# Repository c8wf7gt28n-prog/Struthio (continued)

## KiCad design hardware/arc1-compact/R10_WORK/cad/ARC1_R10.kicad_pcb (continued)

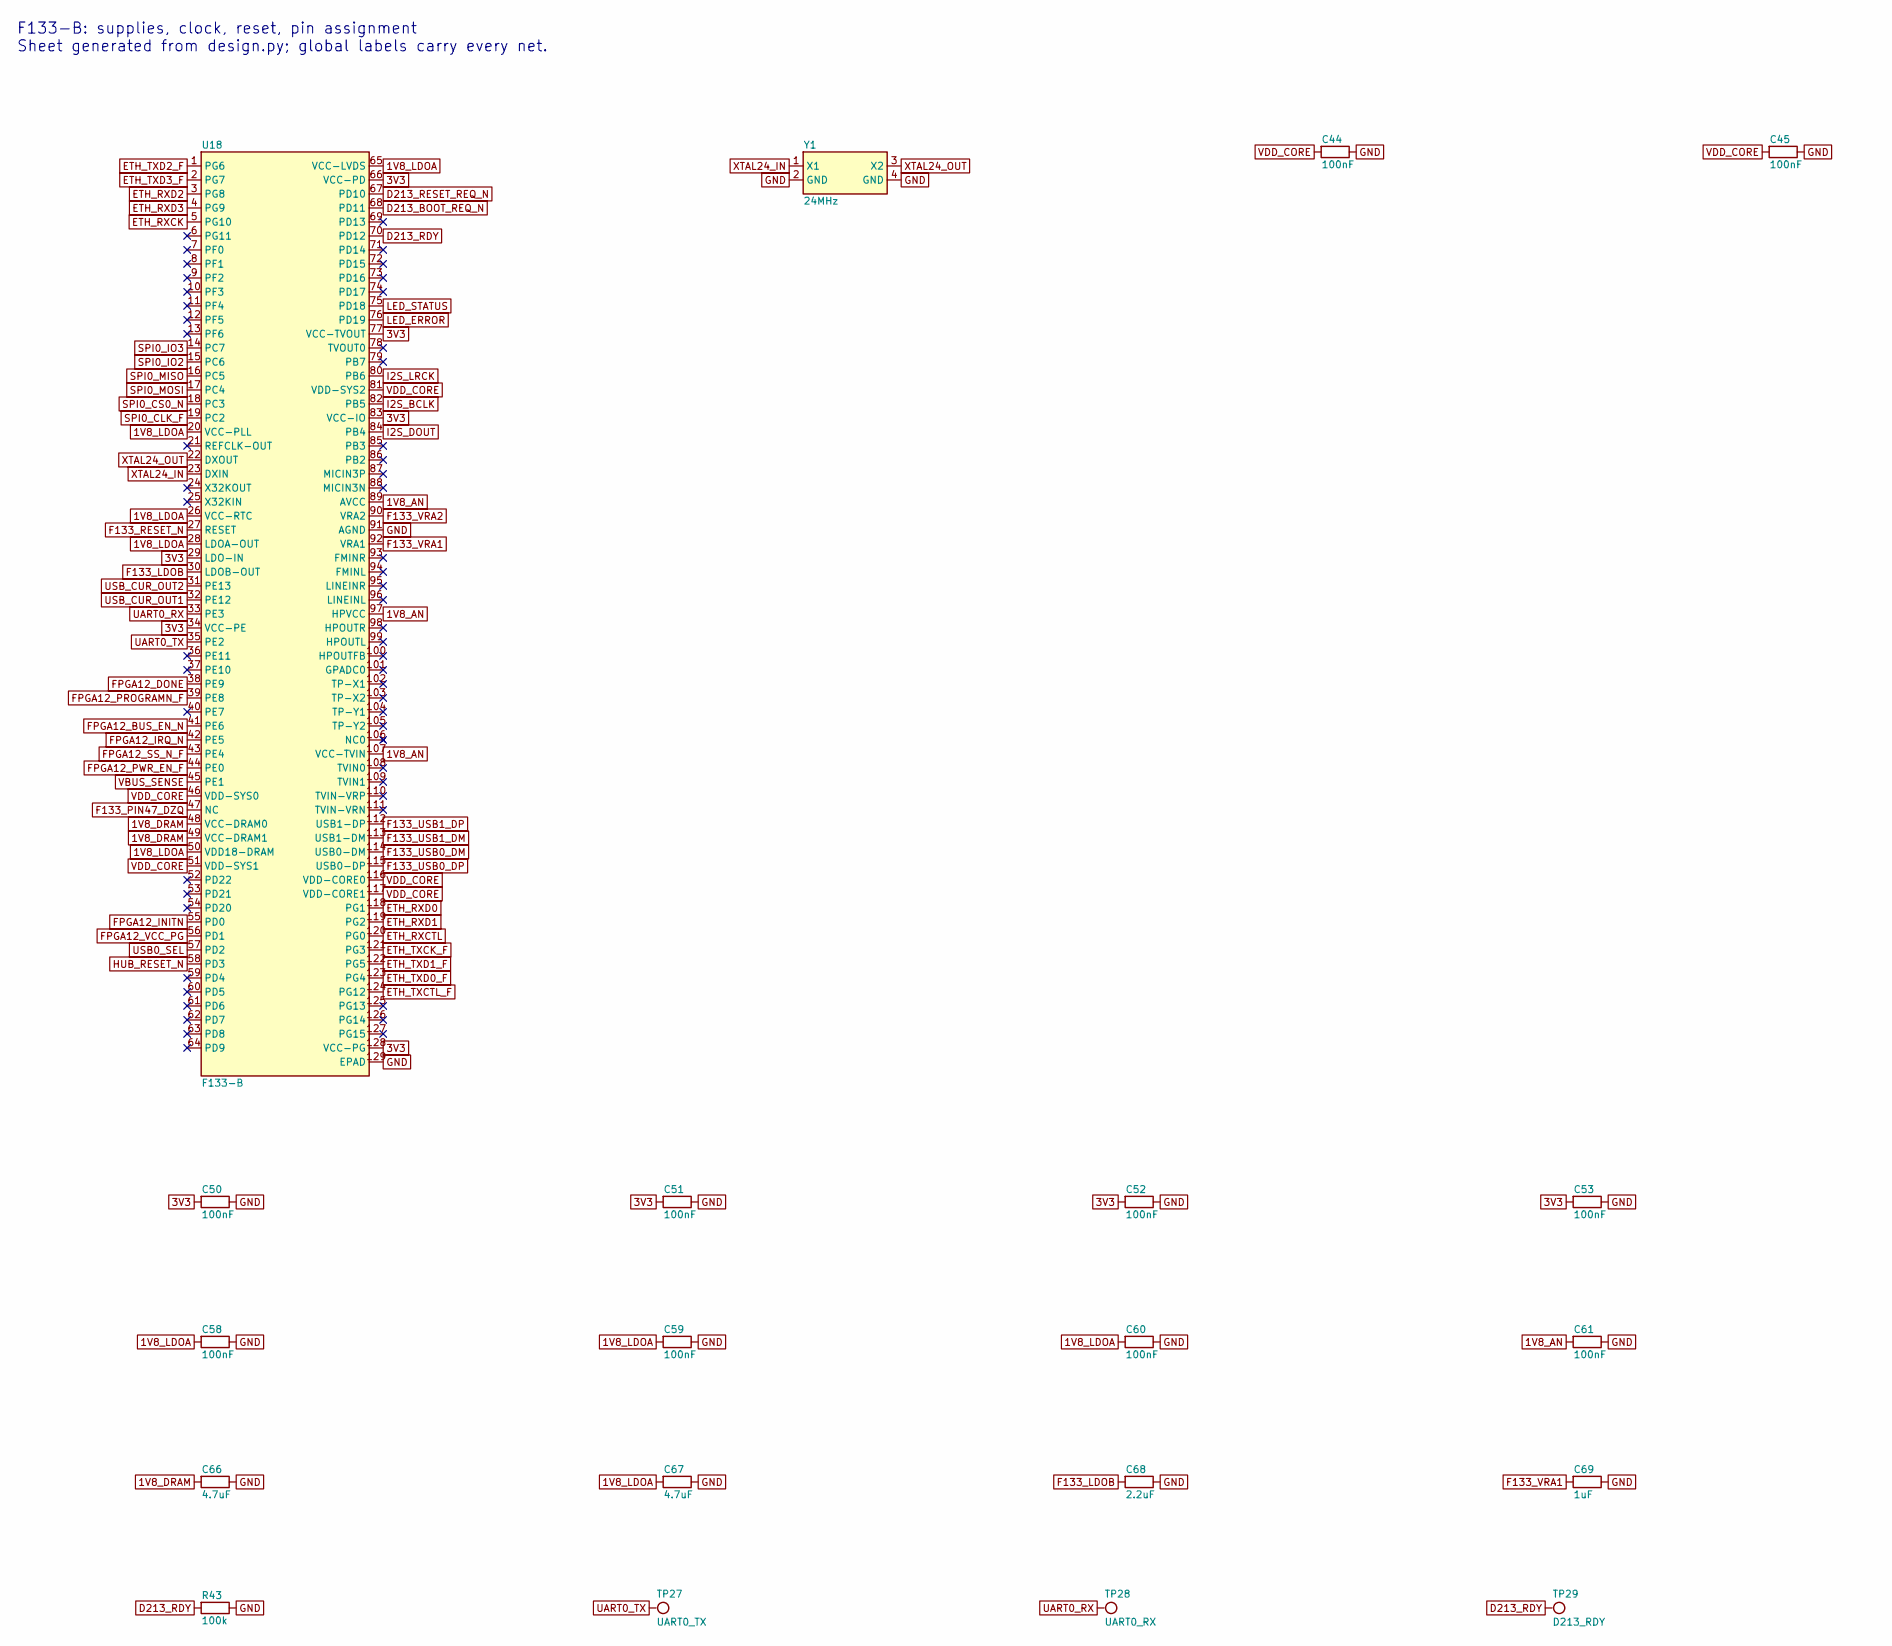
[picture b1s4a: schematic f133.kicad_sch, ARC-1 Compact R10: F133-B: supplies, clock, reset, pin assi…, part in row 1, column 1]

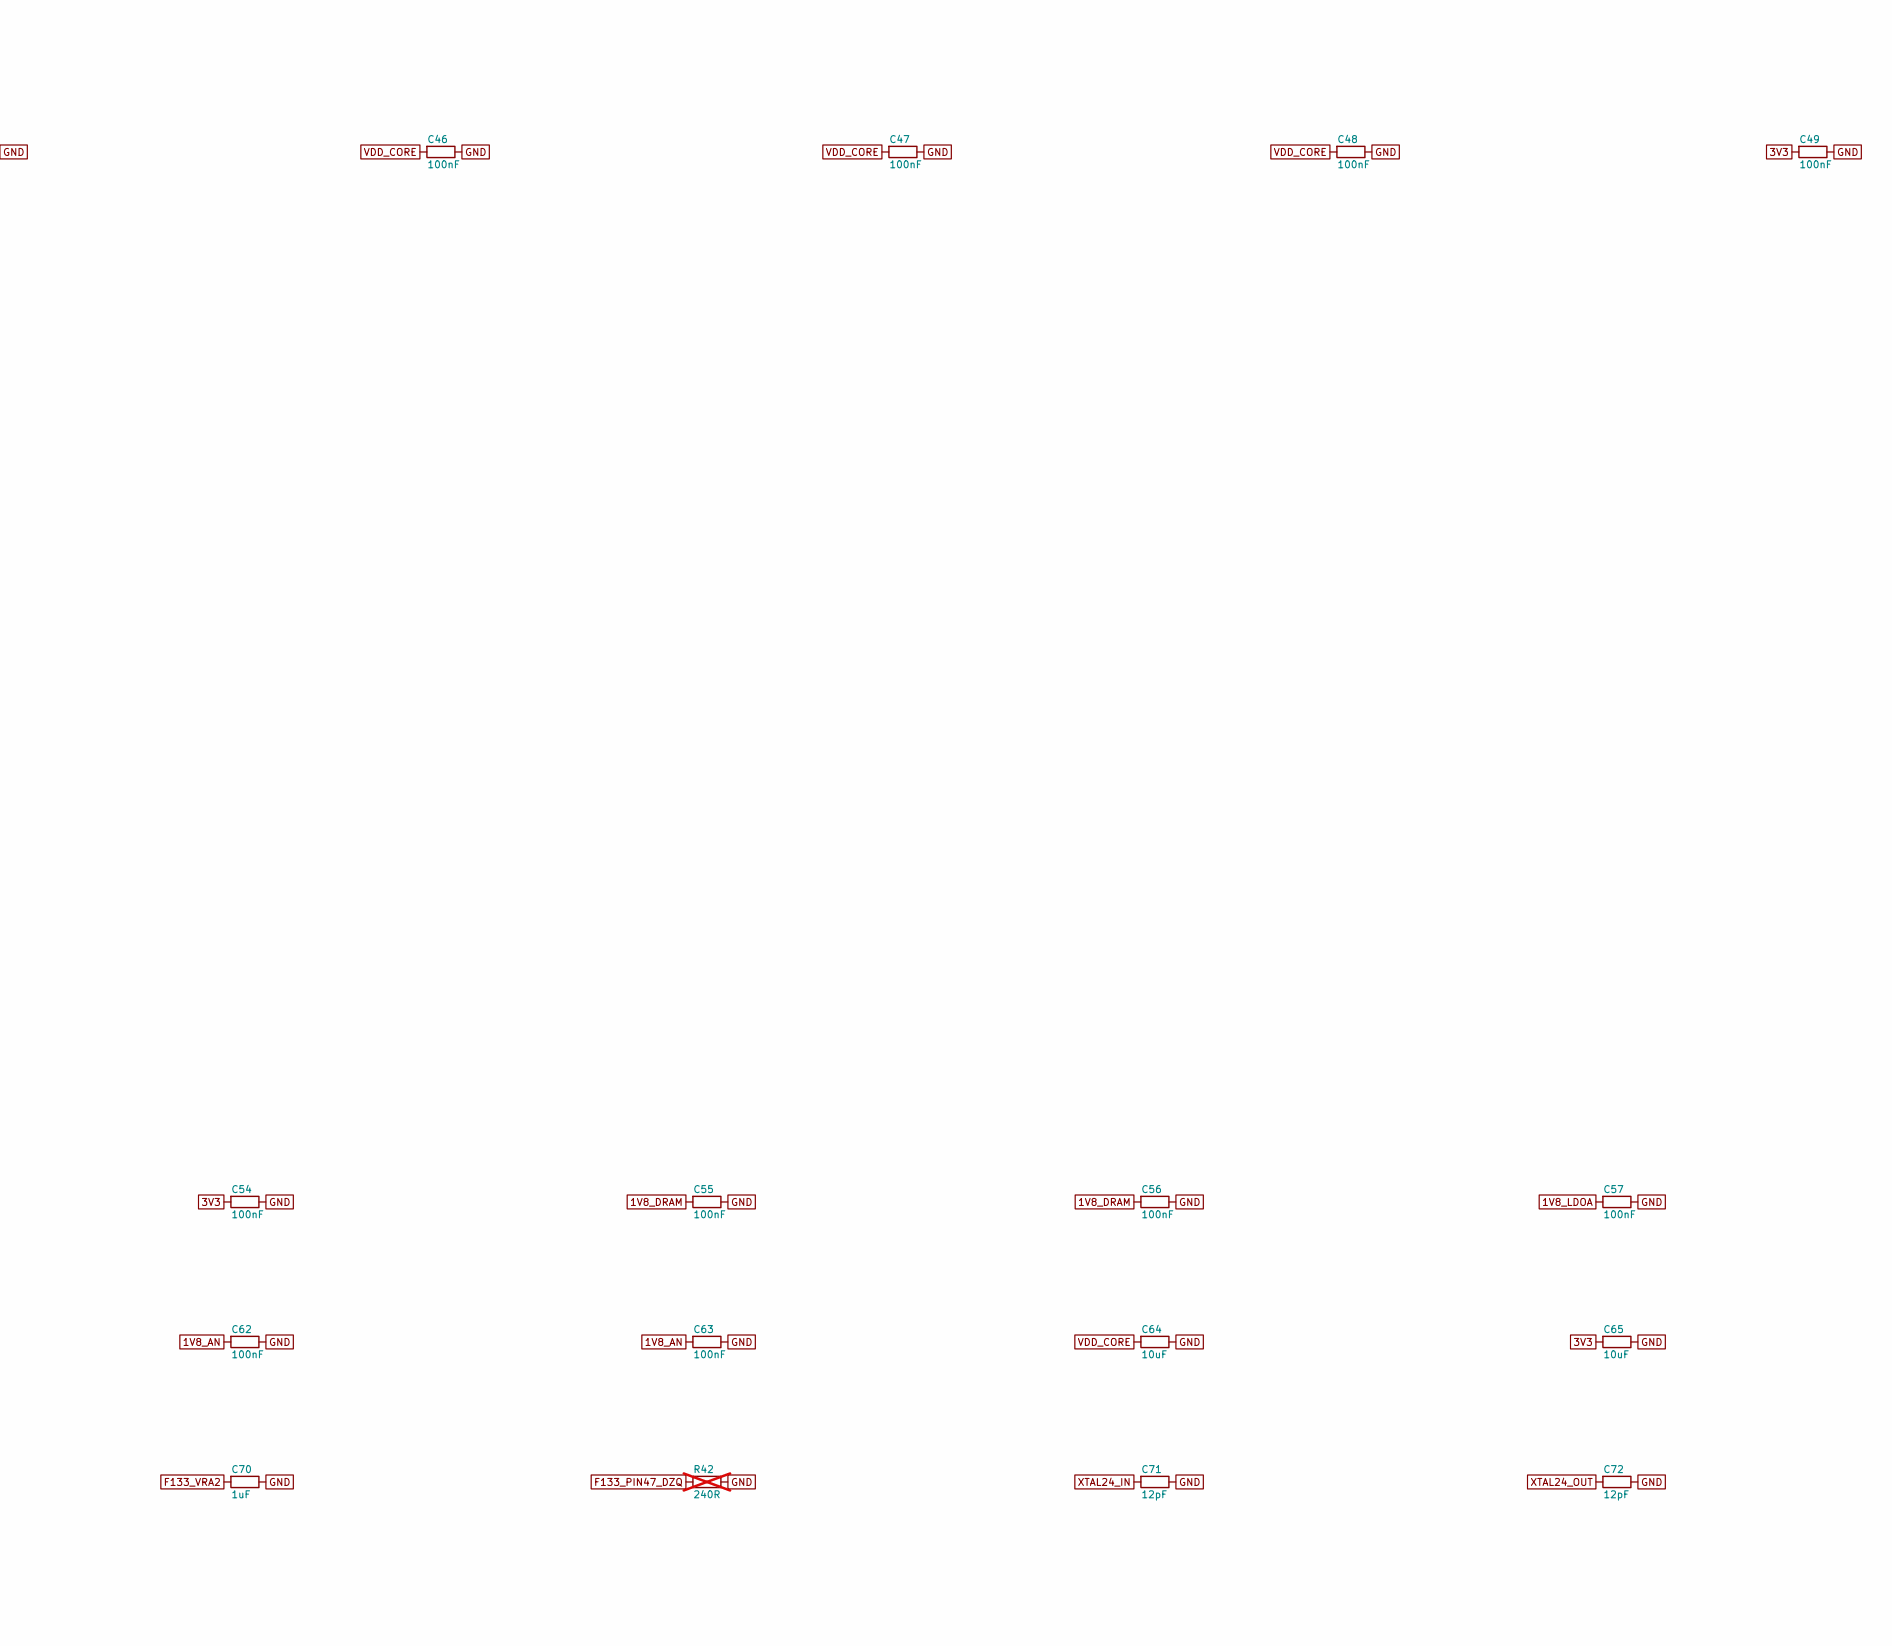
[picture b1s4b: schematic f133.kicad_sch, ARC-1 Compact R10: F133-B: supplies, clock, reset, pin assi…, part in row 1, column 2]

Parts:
C44, C45, C46, C47, C48, C49, C50, C51, C52, C53, C54, C55, C56, C57, C58, C59, C60, C61, C62, C63: 100nF; C_0402_1005Metric; MPN CL05B104KO5NNNC; LCSC C1525
C64, C65: 10uF; C_0603_1608Metric; MPN CL10A106KP8NNNC; LCSC C19702
C66, C67: 4.7uF; C_0603_1608Metric; MPN CL10A475KO8NNNC; LCSC C19666
C68: 2.2uF; C_0603_1608Metric
C69, C70: 1uF; C_0402_1005Metric; MPN CL05A105KA5NQNC; LCSC C52923
C71, C72: 12pF; C_0402_1005Metric; MPN 0402CG120J500NT; LCSC C1547
R42: 240R; R_0402_1005Metric; not fitted
R43: 100k; R_0402_1005Metric; MPN 0402WGF1003TCE; LCSC C25741
TP27: UART0_TX; TestPoint_Pad_D1.0mm
TP28: UART0_RX; TestPoint_Pad_D1.0mm
TP29: D213_RDY; TestPoint_Pad_D1.0mm
U18: F133-B; Allwinner_F133_eLQFP128_14x14_P0.4_EP5.72; MPN F133-B
Y1: 24MHz; Crystal_SMD_3225-4Pin_3.2x2.5mm; MPN 24 MHz 3225 crystal CL=12 pF +-20 ppm (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

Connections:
1V8_AN: C61.1, C62.1, C63.1, U18.89 (AVCC), U18.97 (HPVCC), U18.107 (VCC-TVIN); also elsewhere on the board
1V8_DRAM: C55.1, C56.1, C66.1, U18.48 (VCC-DRAM0), U18.49 (VCC-DRAM1); also elsewhere on the board
1V8_LDOA: C57.1, C58.1, C59.1, C60.1, C67.1, U18.20 (VCC-PLL), U18.26 (VCC-RTC), U18.28 (LDOA-OUT), U18.50 (VDD18-DRAM), U18.65 (VCC-LVDS); also elsewhere on the board
3V3: C49.1, C50.1, C51.1, C52.1, C53.1, C54.1, C65.1, U18.29 (LDO-IN), U18.34 (VCC-PE), U18.66 (VCC-PD), U18.77 (VCC-TVOUT), U18.83 (VCC-IO), U18.128 (VCC-PG); also elsewhere on the board
D213_BOOT_REQ_N: U18.68 (PD11); also elsewhere on the board
D213_RDY: R43.1, TP29.1, U18.70 (PD12); also elsewhere on the board
D213_RESET_REQ_N: U18.67 (PD10); also elsewhere on the board
ETH_RXCK: U18.5 (PG10); also elsewhere on the board
ETH_RXCTL: U18.120 (PG0); also elsewhere on the board
ETH_RXD0: U18.118 (PG1); also elsewhere on the board
ETH_RXD1: U18.119 (PG2); also elsewhere on the board
ETH_RXD2: U18.3 (PG8); also elsewhere on the board
ETH_RXD3: U18.4 (PG9); also elsewhere on the board
ETH_TXCK_F: U18.121 (PG3); also elsewhere on the board
ETH_TXCTL_F: U18.124 (PG12); also elsewhere on the board
ETH_TXD0_F: U18.123 (PG4); also elsewhere on the board
ETH_TXD1_F: U18.122 (PG5); also elsewhere on the board
ETH_TXD2_F: U18.1 (PG6); also elsewhere on the board
ETH_TXD3_F: U18.2 (PG7); also elsewhere on the board
F133_LDOB: C68.1, U18.30 (LDOB-OUT)
F133_PIN47_DZQ: R42.1, U18.47 (NC)
F133_RESET_N: U18.27 (RESET); also elsewhere on the board
F133_USB0_DM: U18.114 (USB0-DM); also elsewhere on the board
F133_USB0_DP: U18.115 (USB0-DP); also elsewhere on the board
F133_USB1_DM: U18.113 (USB1-DM); also elsewhere on the board
F133_USB1_DP: U18.112 (USB1-DP); also elsewhere on the board
F133_VRA1: C69.1, U18.92 (VRA1)
F133_VRA2: C70.1, U18.90 (VRA2)
FPGA12_BUS_EN_N: U18.41 (PE6); also elsewhere on the board
FPGA12_DONE: U18.38 (PE9); also elsewhere on the board
FPGA12_INITN: U18.55 (PD0); also elsewhere on the board
FPGA12_IRQ_N: U18.42 (PE5); also elsewhere on the board
FPGA12_PROGRAMN_F: U18.39 (PE8); also elsewhere on the board
FPGA12_PWR_EN_F: U18.44 (PE0); also elsewhere on the board
FPGA12_SS_N_F: U18.43 (PE4); also elsewhere on the board
FPGA12_VCC_PG: U18.56 (PD1); also elsewhere on the board
GND: C44.2, C45.2, C46.2, C47.2, C48.2, C49.2, C50.2, C51.2, C52.2, C53.2, C54.2, C55.2, C56.2, C57.2, C58.2, C59.2, C60.2, C61.2, C62.2, C63.2, C64.2, C65.2, C66.2, C67.2, C68.2, C69.2, C70.2, C71.2, C72.2, R42.2, R43.2, U18.91 (AGND), U18.129 (EPAD), Y1.2 (GND), Y1.4 (GND); also elsewhere on the board
HUB_RESET_N: U18.58 (PD3); also elsewhere on the board
I2S_BCLK: U18.82 (PB5); also elsewhere on the board
I2S_DOUT: U18.84 (PB4); also elsewhere on the board
I2S_LRCK: U18.80 (PB6); also elsewhere on the board
LED_ERROR: U18.76 (PD19); also elsewhere on the board
LED_STATUS: U18.75 (PD18); also elsewhere on the board
SPI0_CLK_F: U18.19 (PC2); also elsewhere on the board
SPI0_CS0_N: U18.18 (PC3); also elsewhere on the board
SPI0_IO2: U18.15 (PC6); also elsewhere on the board
SPI0_IO3: U18.14 (PC7); also elsewhere on the board
SPI0_MISO: U18.16 (PC5); also elsewhere on the board
SPI0_MOSI: U18.17 (PC4); also elsewhere on the board
UART0_RX: TP28.1, U18.33 (PE3); also elsewhere on the board
UART0_TX: TP27.1, U18.35 (PE2); also elsewhere on the board
USB0_SEL: U18.57 (PD2); also elsewhere on the board
USB_CUR_OUT1: U18.32 (PE12); also elsewhere on the board
USB_CUR_OUT2: U18.31 (PE13); also elsewhere on the board
VBUS_SENSE: U18.45 (PE1); also elsewhere on the board
VDD_CORE: C44.1, C45.1, C46.1, C47.1, C48.1, C64.1, U18.46 (VDD-SYS0), U18.51 (VDD-SYS1), U18.81 (VDD-SYS2), U18.116 (VDD-CORE0), U18.117 (VDD-CORE1); also elsewhere on the board
XTAL24_IN: C71.1, U18.23 (DXIN), Y1.1 (X1)
XTAL24_OUT: C72.1, U18.22 (DXOUT), Y1.3 (X2)

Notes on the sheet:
F133-B: supplies, clock, reset, pin assignment Sheet generated from design.py; global labels carry every net.

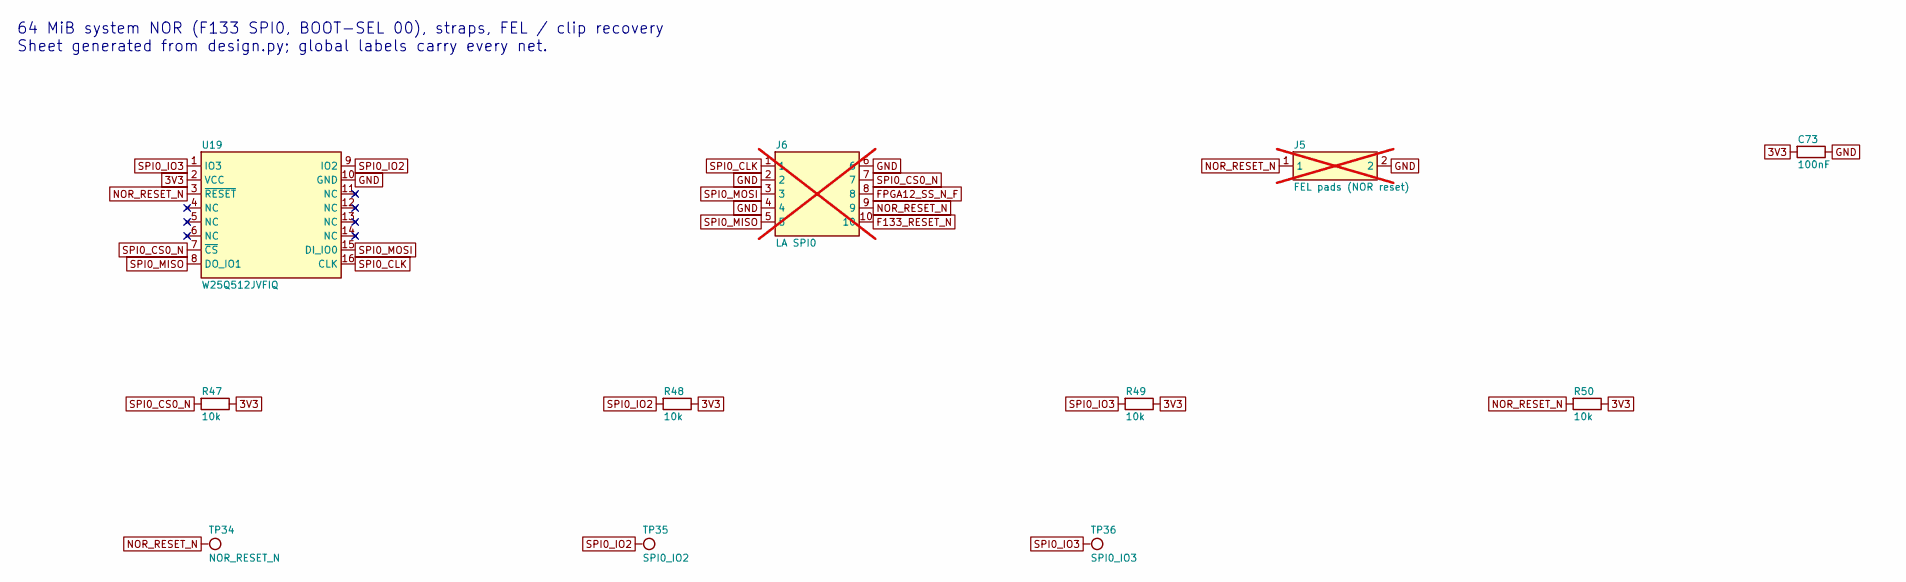
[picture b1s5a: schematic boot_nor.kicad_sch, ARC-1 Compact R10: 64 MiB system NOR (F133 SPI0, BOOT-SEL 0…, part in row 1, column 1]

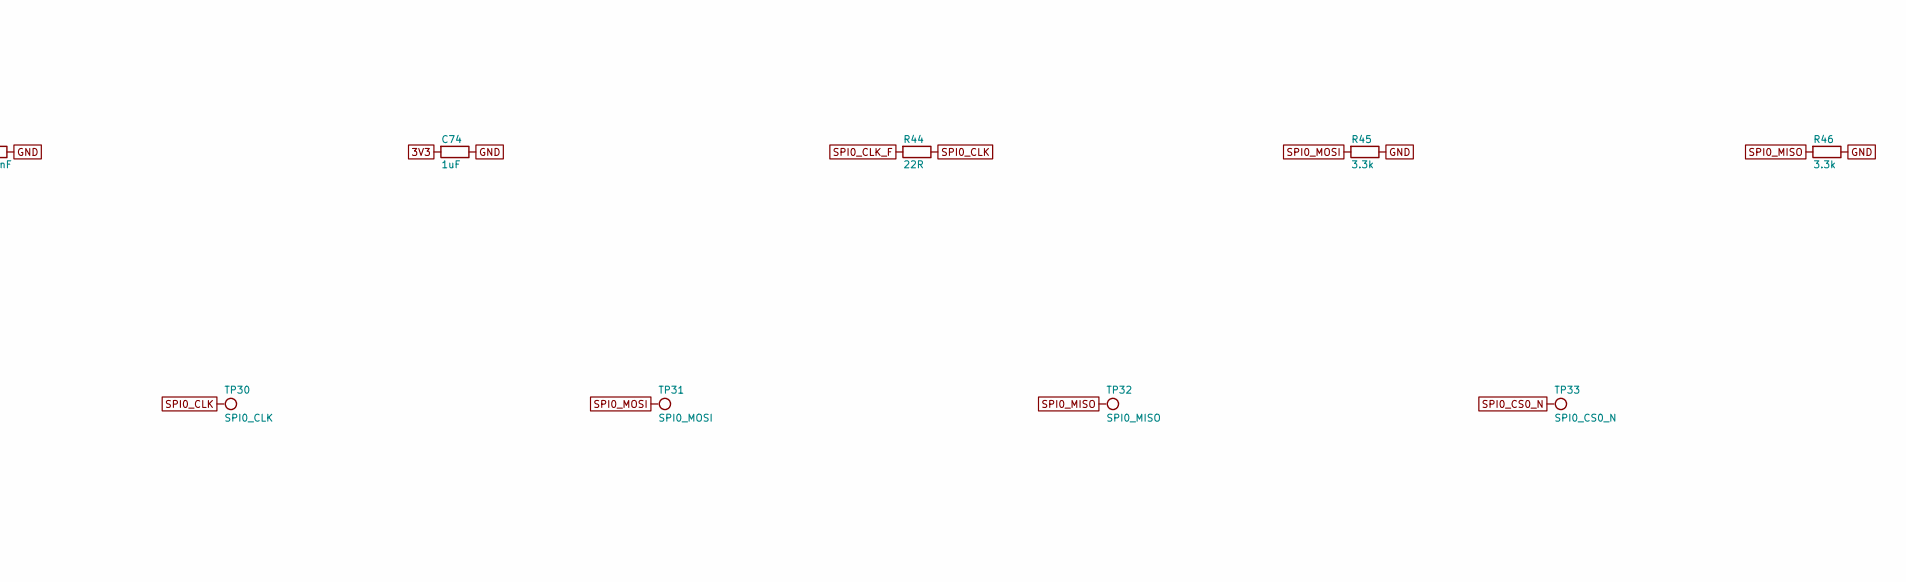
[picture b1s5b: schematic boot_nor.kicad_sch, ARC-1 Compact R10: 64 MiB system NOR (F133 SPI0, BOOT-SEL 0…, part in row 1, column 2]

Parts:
C73: 100nF; C_0402_1005Metric; MPN CL05B104KO5NNNC; LCSC C1525
C74: 1uF; C_0402_1005Metric; MPN CL05A105KA5NQNC; LCSC C52923
J5: FEL pads (NOR reset); TestPoint_2Pads_Pitch2.54mm_Drill0.8mm; MPN internal service pad pair; not fitted
J6: LA SPI0; PinHeader_2x05_P1.27mm_Vertical_SMD; MPN header 2x5 1.27 SMD; not fitted
R44: 22R; R_0402_1005Metric; MPN 0402WGF220JTCE; LCSC C25092
R45, R46: 3.3k; R_0402_1005Metric
R47, R48, R49, R50: 10k; R_0402_1005Metric; MPN 0402WGF1002TCE; LCSC C25744
TP30: SPI0_CLK; TestPoint_Pad_D1.0mm
TP31: SPI0_MOSI; TestPoint_Pad_D1.0mm
TP32: SPI0_MISO; TestPoint_Pad_D1.0mm
TP33: SPI0_CS0_N; TestPoint_Pad_D1.0mm
TP34: NOR_RESET_N; TestPoint_Pad_D1.0mm
TP35: SPI0_IO2; TestPoint_Pad_D1.0mm
TP36: SPI0_IO3; TestPoint_Pad_D1.0mm
U19: W25Q512JVFIQ; SOIC-16W_7.5x10.3mm_P1.27mm; MPN W25Q512JVFIQ

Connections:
3V3: C73.1, C74.1, R47.2, R48.2, R49.2, R50.2, U19.2 (VCC); also elsewhere on the board
F133_RESET_N: J6.10; also elsewhere on the board
FPGA12_SS_N_F: J6.8; also elsewhere on the board
GND: C73.2, C74.2, J5.2, J6.2, J6.4, J6.6, R45.2, R46.2, U19.10 (GND); also elsewhere on the board
NOR_RESET_N: J5.1, J6.9, R50.1, TP34.1, U19.3 (~RESET)
SPI0_CLK: J6.1, R44.2, TP30.1, U19.16 (CLK); also elsewhere on the board
SPI0_CLK_F: R44.1; also elsewhere on the board
SPI0_CS0_N: J6.7, R47.1, TP33.1, U19.7 (~CS); also elsewhere on the board
SPI0_IO2: R48.1, TP35.1, U19.9 (IO2); also elsewhere on the board
SPI0_IO3: R49.1, TP36.1, U19.1 (IO3); also elsewhere on the board
SPI0_MISO: J6.5, R46.1, TP32.1, U19.8 (DO_IO1); also elsewhere on the board
SPI0_MOSI: J6.3, R45.1, TP31.1, U19.15 (DI_IO0); also elsewhere on the board

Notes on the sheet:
64 MiB system NOR (F133 SPI0, BOOT-SEL 00), straps, FEL / clip recovery Sheet generated from design.py; global labels carry every net.
